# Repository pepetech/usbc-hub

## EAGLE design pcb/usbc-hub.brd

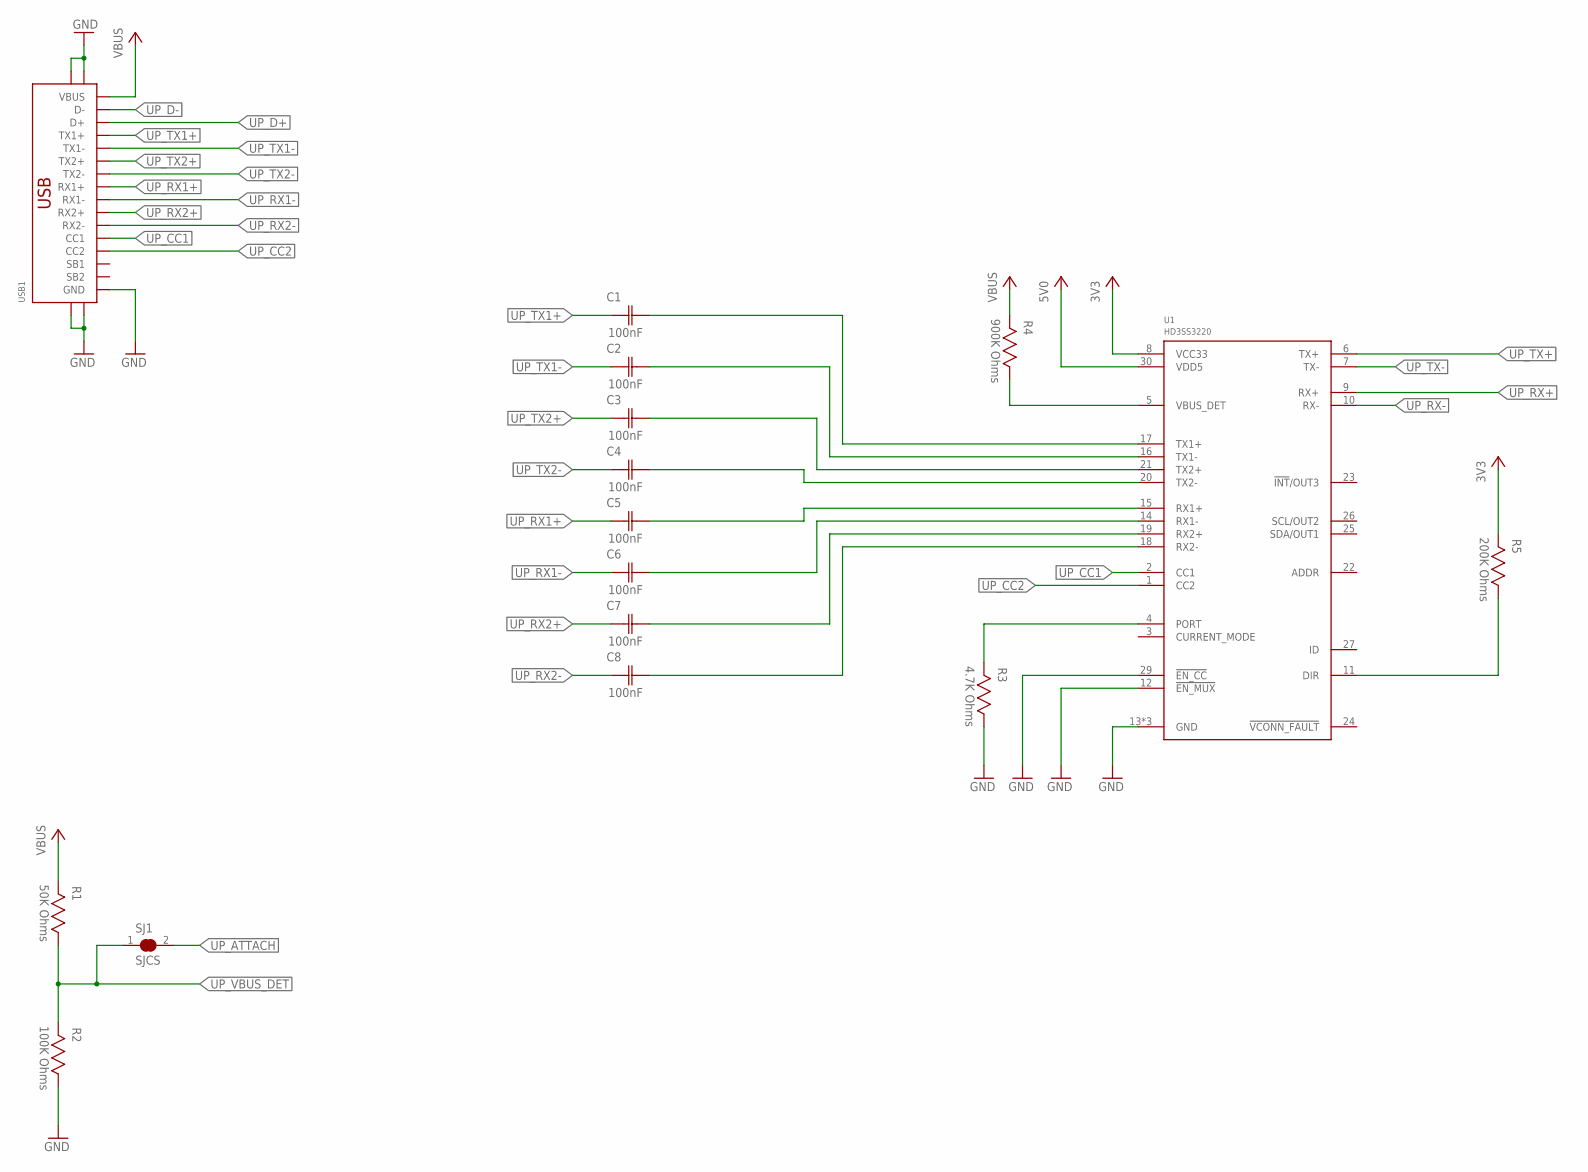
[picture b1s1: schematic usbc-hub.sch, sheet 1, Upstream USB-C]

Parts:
C1, C2, C3, C4, C5, C6, C7, C8: 100nF; CAP0603
R1: 50K Ohms; RES0603
R2: 100K Ohms; RES0603
R3: 4.7K Ohms; RES0603
R4: 900K Ohms; RES0603
R5: 200K Ohms; RES0603
SJ1: SJCS; SJC_S
U1: HD3SS3220; WQFN30
USB1: USB-C-24P-SMD-FLAT-SIDE

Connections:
3V3: R5.2, U1.8 (VCC33); also elsewhere on the board
5V0: U1.30 (VDD5); also elsewhere on the board
DN2_PWR_EN1: R1.2
GND: R2.1, R3.1, U1.12 (!EN_MUX), U1.13 (GND), U1.28 (GND), U1.29 (!EN_CC), U1.31 (GND), USB1.A1 (GND), USB1.A12 (GND), USB1.B1 (GND), USB1.B12 (GND), USB1.SHIELD@0 (SHIELD), USB1.SHIELD@1 (SHIELD), USB1.SHIELD@2 (SHIELD), USB1.SHIELD@3 (SHIELD); also elsewhere on the board
unnamed: C1.2 (C2), U1.17 (TX1+)
unnamed: C2.2 (C2), U1.16 (TX1-)
unnamed: C3.2 (C2), U1.21 (TX2+)
unnamed: C4.2 (C2), U1.20 (TX2-)
unnamed: C5.2 (C2), U1.15 (RX1+)
unnamed: C6.2 (C2), U1.14 (RX1-)
unnamed: C7.2 (C2), U1.19 (RX2+)
unnamed: C8.2 (C2), U1.18 (RX2-)
unnamed: R4.1, U1.5 (VBUS_DET)
unnamed: R3.2, U1.4 (PORT)
unnamed: R5.1, U1.11 (DIR)
UP_ATTACH: SJ1.2; also elsewhere on the board
UP_CC1: U1.2 (CC1), USB1.A5 (CC1)
UP_CC2: U1.1 (CC2), USB1.B5 (CC2)
UP_D+: USB1.A6 (D+), USB1.B6 (D+); also elsewhere on the board
UP_D-: USB1.A7 (D-), USB1.B7 (D-); also elsewhere on the board
UP_RX1+: C5.1 (C1), USB1.B11 (RX1+)
UP_RX1-: C6.1 (C1), USB1.B10 (RX1-)
UP_RX2+: C7.1 (C1), USB1.A11 (RX2+)
UP_RX2-: C8.1 (C1), USB1.A10 (RX2-)
UP_RX+: U1.9 (RX+); also elsewhere on the board
UP_RX-: U1.10 (RX-); also elsewhere on the board
UP_TX1+: C1.1 (C1), USB1.A2 (TX1+)
UP_TX1-: C2.1 (C1), USB1.A3 (TX1-)
UP_TX2+: C3.1 (C1), USB1.B2 (TX2+)
UP_TX2-: C4.1 (C1), USB1.B3 (TX2-)
UP_TX+: U1.6 (TX+); also elsewhere on the board
UP_TX-: U1.7 (TX-); also elsewhere on the board
UP_VBUS_DET: R1.1, R2.2, SJ1.1; also elsewhere on the board
VBUS: R4.2, USB1.A4 (VBUS), USB1.A9 (VBUS), USB1.B4 (VBUS), USB1.B9 (VBUS); also elsewhere on the board

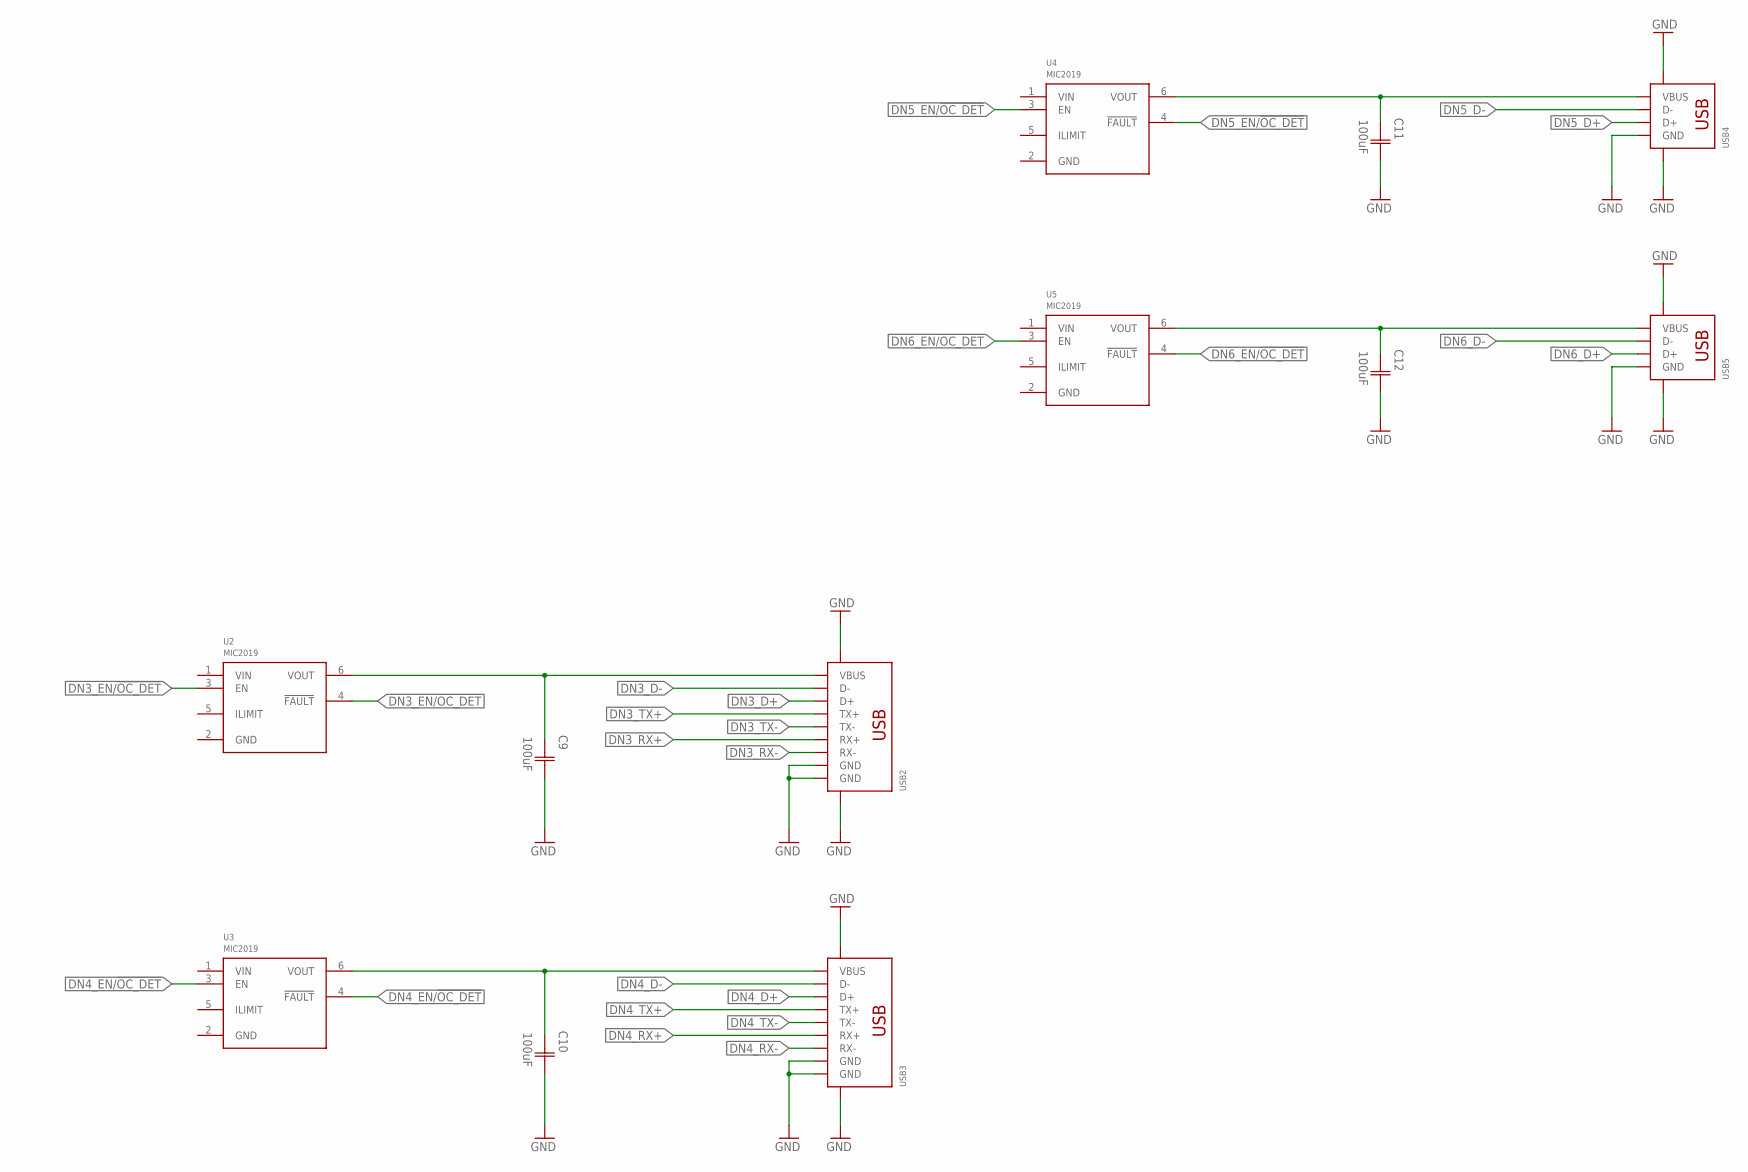
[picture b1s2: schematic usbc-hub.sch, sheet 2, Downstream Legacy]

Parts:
C9, C10, C11, C12: 100uF; CAP1206
U2, U3, U4, U5: MIC2019; SOT23-6
USB2, USB3: USB3-A-TH-FLAT-SIDE
USB4, USB5: USB-A-TH-FLAT-SIDE

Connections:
DN3_D+: USB2.D+; also elsewhere on the board
DN3_D-: USB2.D-; also elsewhere on the board
DN3_EN/!OC_DET: U2.3 (EN), U2.4 (!FAULT); also elsewhere on the board
DN3_RX+: USB2.RX+; also elsewhere on the board
DN3_RX-: USB2.RX-; also elsewhere on the board
DN3_TX+: USB2.TX+; also elsewhere on the board
DN3_TX-: USB2.TX-; also elsewhere on the board
DN4_D+: USB3.D+; also elsewhere on the board
DN4_D-: USB3.D-; also elsewhere on the board
DN4_EN/!OC_DET: U3.3 (EN), U3.4 (!FAULT); also elsewhere on the board
DN4_RX+: USB3.RX+; also elsewhere on the board
DN4_RX-: USB3.RX-; also elsewhere on the board
DN4_TX+: USB3.TX+; also elsewhere on the board
DN4_TX-: USB3.TX-; also elsewhere on the board
DN5_D+: USB4.D+; also elsewhere on the board
DN5_D-: USB4.D-; also elsewhere on the board
DN5_EN/!OC_DET: U4.3 (EN), U4.4 (!FAULT); also elsewhere on the board
DN6_D+: USB5.D+; also elsewhere on the board
DN6_D-: USB5.D-; also elsewhere on the board
DN6_EN/!OC_DET: U5.3 (EN), U5.4 (!FAULT); also elsewhere on the board
GND: C9.2 (C2), C10.2 (C2), C11.2 (C2), C12.2 (C2), USB2.GND, USB2.P$10 (SHIELD), USB2.P$11 (SHIELD), USB2.SS_GND (GND), USB3.GND, USB3.P$10 (SHIELD), USB3.P$11 (SHIELD), USB3.SS_GND (GND), USB4.GND, USB4.P$5 (SHIELD), USB4.P$6 (SHIELD), USB5.GND, USB5.P$5 (SHIELD), USB5.P$6 (SHIELD); also elsewhere on the board
unnamed: C9.1 (C1), U2.6 (VOUT), USB2.VBUS
unnamed: C12.1 (C1), U5.6 (VOUT), USB5.VBUS
unnamed: C11.1 (C1), U4.6 (VOUT), USB4.VBUS
unnamed: C10.1 (C1), U3.6 (VOUT), USB3.VBUS

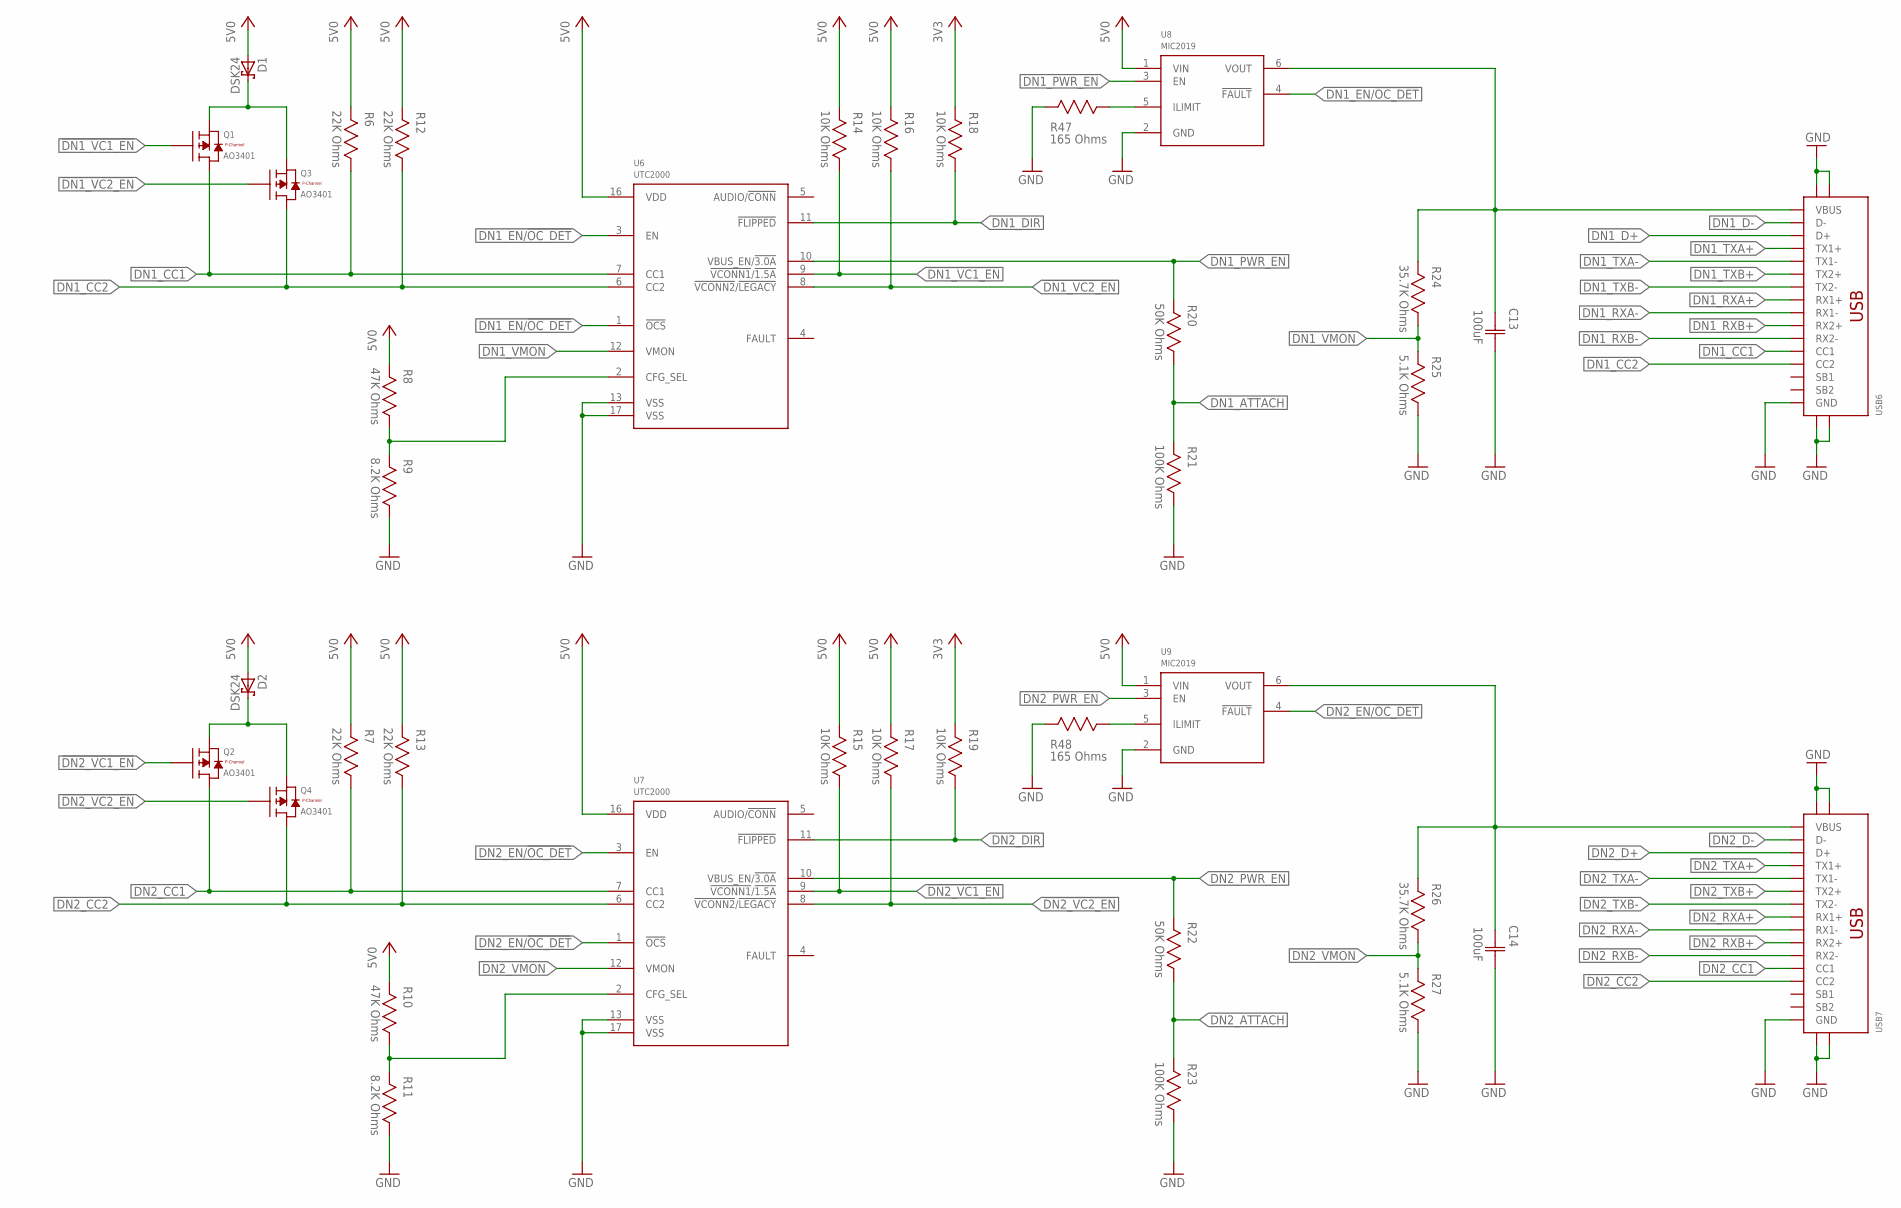
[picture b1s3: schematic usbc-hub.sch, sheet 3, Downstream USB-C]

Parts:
C13, C14: 100uF; CAP1206
D1, D2: DSK24; SOD-123F
Q1, Q2, Q3, Q4: AO3401; SOT23
R6, R7, R12, R13: 22K Ohms; RES0603
R8, R10: 47K Ohms; RES0603
R9, R11: 8.2K Ohms; RES0603
R14, R15, R16, R17, R18, R19: 10K Ohms; RES0603
R20, R22: 50K Ohms; RES0603
R21, R23: 100K Ohms; RES0603
R24, R26: 35.7K Ohms; RES0603
R25, R27: 5.1K Ohms; RES0603
R47, R48: 165 Ohms; RES0603
U6, U7: UTC2000; QFN16
U8, U9: MIC2019; SOT23-6
USB6, USB7: USB-C-24P-SMD-FLAT-SIDE

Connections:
3V3: R18.2, R19.2; also elsewhere on the board
5V0: D1.A, D2.A, R6.2, R7.2, R8.2, R10.2, R12.2, R13.2, R14.2, R15.2, R16.2, R17.2, U6.16 (VDD), U7.16 (VDD), U8.1 (VIN), U9.1 (VIN); also elsewhere on the board
!DN1_VC1_EN: Q1.1 (G), R14.1, U6.9 (!VCONN1!/!1.5A)
!DN1_VC2_EN: Q3.1 (G), R16.1, U6.8 (!VCONN2!/!LEGACY)
!DN2_VC1_EN: Q2.1 (G), R15.1, U7.9 (!VCONN1!/!1.5A)
!DN2_VC2_EN: Q4.1 (G), R17.1, U7.8 (!VCONN2!/!LEGACY)
DN1_ATTACH: R20.1, R21.2; also elsewhere on the board
DN1_CC1: Q1.3 (D), R6.1, U6.7 (CC1), USB6.A5 (CC1)
DN1_CC2: Q3.3 (D), R12.1, U6.6 (CC2), USB6.B5 (CC2)
DN1_D+: USB6.A6 (D+), USB6.B6 (D+); also elsewhere on the board
DN1_D-: USB6.A7 (D-), USB6.B7 (D-); also elsewhere on the board
DN1_DIR: R18.1, U6.11 (!FLIPPED); also elsewhere on the board
DN1_EN/!OC_DET: U6.1 (!OCS), U6.3 (EN), U8.4 (!FAULT); also elsewhere on the board
DN1_PWR_EN: R20.2, U6.10 (VBUS_EN/!3.0A), U8.3 (EN)
DN1_RXA+: USB6.B11 (RX1+); also elsewhere on the board
DN1_RXA-: USB6.B10 (RX1-); also elsewhere on the board
DN1_RXB+: USB6.A11 (RX2+); also elsewhere on the board
DN1_RXB-: USB6.A10 (RX2-); also elsewhere on the board
DN1_TXA+: USB6.A2 (TX1+); also elsewhere on the board
DN1_TXA-: USB6.A3 (TX1-); also elsewhere on the board
DN1_TXB+: USB6.B2 (TX2+); also elsewhere on the board
DN1_TXB-: USB6.B3 (TX2-); also elsewhere on the board
DN1_VMON: R24.1, R25.2, U6.12 (VMON)
DN2_ATTACH: R22.1, R23.2; also elsewhere on the board
DN2_CC1: Q2.3 (D), R7.1, U7.7 (CC1), USB7.A5 (CC1)
DN2_CC2: Q4.3 (D), R13.1, U7.6 (CC2), USB7.B5 (CC2)
DN2_D+: USB7.A6 (D+), USB7.B6 (D+); also elsewhere on the board
DN2_D-: USB7.A7 (D-), USB7.B7 (D-); also elsewhere on the board
DN2_DIR: R19.1, U7.11 (!FLIPPED); also elsewhere on the board
DN2_EN/!OC_DET: U7.1 (!OCS), U7.3 (EN), U9.4 (!FAULT); also elsewhere on the board
DN2_PWR_EN: R22.2, U7.10 (VBUS_EN/!3.0A), U9.3 (EN)
DN2_RXA+: USB7.B11 (RX1+); also elsewhere on the board
DN2_RXA-: USB7.B10 (RX1-); also elsewhere on the board
DN2_RXB+: USB7.A11 (RX2+); also elsewhere on the board
DN2_RXB-: USB7.A10 (RX2-); also elsewhere on the board
DN2_TXA+: USB7.A2 (TX1+); also elsewhere on the board
DN2_TXA-: USB7.A3 (TX1-); also elsewhere on the board
DN2_TXB+: USB7.B2 (TX2+); also elsewhere on the board
DN2_TXB-: USB7.B3 (TX2-); also elsewhere on the board
DN2_VMON: R26.1, R27.2, U7.12 (VMON)
GND: C13.2 (C2), C14.2 (C2), R9.1, R11.1, R21.1, R23.1, R25.1, R27.1, R47.2, R48.2, U6.13 (VSS), U6.17 (VSS), U7.13 (VSS), U7.17 (VSS), U8.2 (GND), U9.2 (GND), USB6.A1 (GND), USB6.A12 (GND), USB6.B1 (GND), USB6.B12 (GND), USB6.SHIELD@0 (SHIELD), USB6.SHIELD@1 (SHIELD), USB6.SHIELD@2 (SHIELD), USB6.SHIELD@3 (SHIELD), USB7.A1 (GND), USB7.A12 (GND), USB7.B1 (GND), USB7.B12 (GND), USB7.SHIELD@0 (SHIELD), USB7.SHIELD@1 (SHIELD), USB7.SHIELD@2 (SHIELD), USB7.SHIELD@3 (SHIELD); also elsewhere on the board
unnamed: C14.1 (C1), U9.6 (VOUT), USB7.A4 (VBUS), USB7.A9 (VBUS), USB7.B4 (VBUS), USB7.B9 (VBUS)
unnamed: C13.1 (C1), R24.2, U8.6 (VOUT), USB6.A4 (VBUS), USB6.A9 (VBUS), USB6.B4 (VBUS), USB6.B9 (VBUS)
unnamed: D2.C, Q2.2 (S), Q4.2 (S)
unnamed: D1.C, Q1.2 (S), Q3.2 (S)
unnamed: R10.1, R11.2, U7.2 (CFG_SEL)
unnamed: R8.1, R9.2, U6.2 (CFG_SEL)
unnamed: R47.1, U8.5 (ILIMIT)
unnamed: R48.1, U9.5 (ILIMIT)

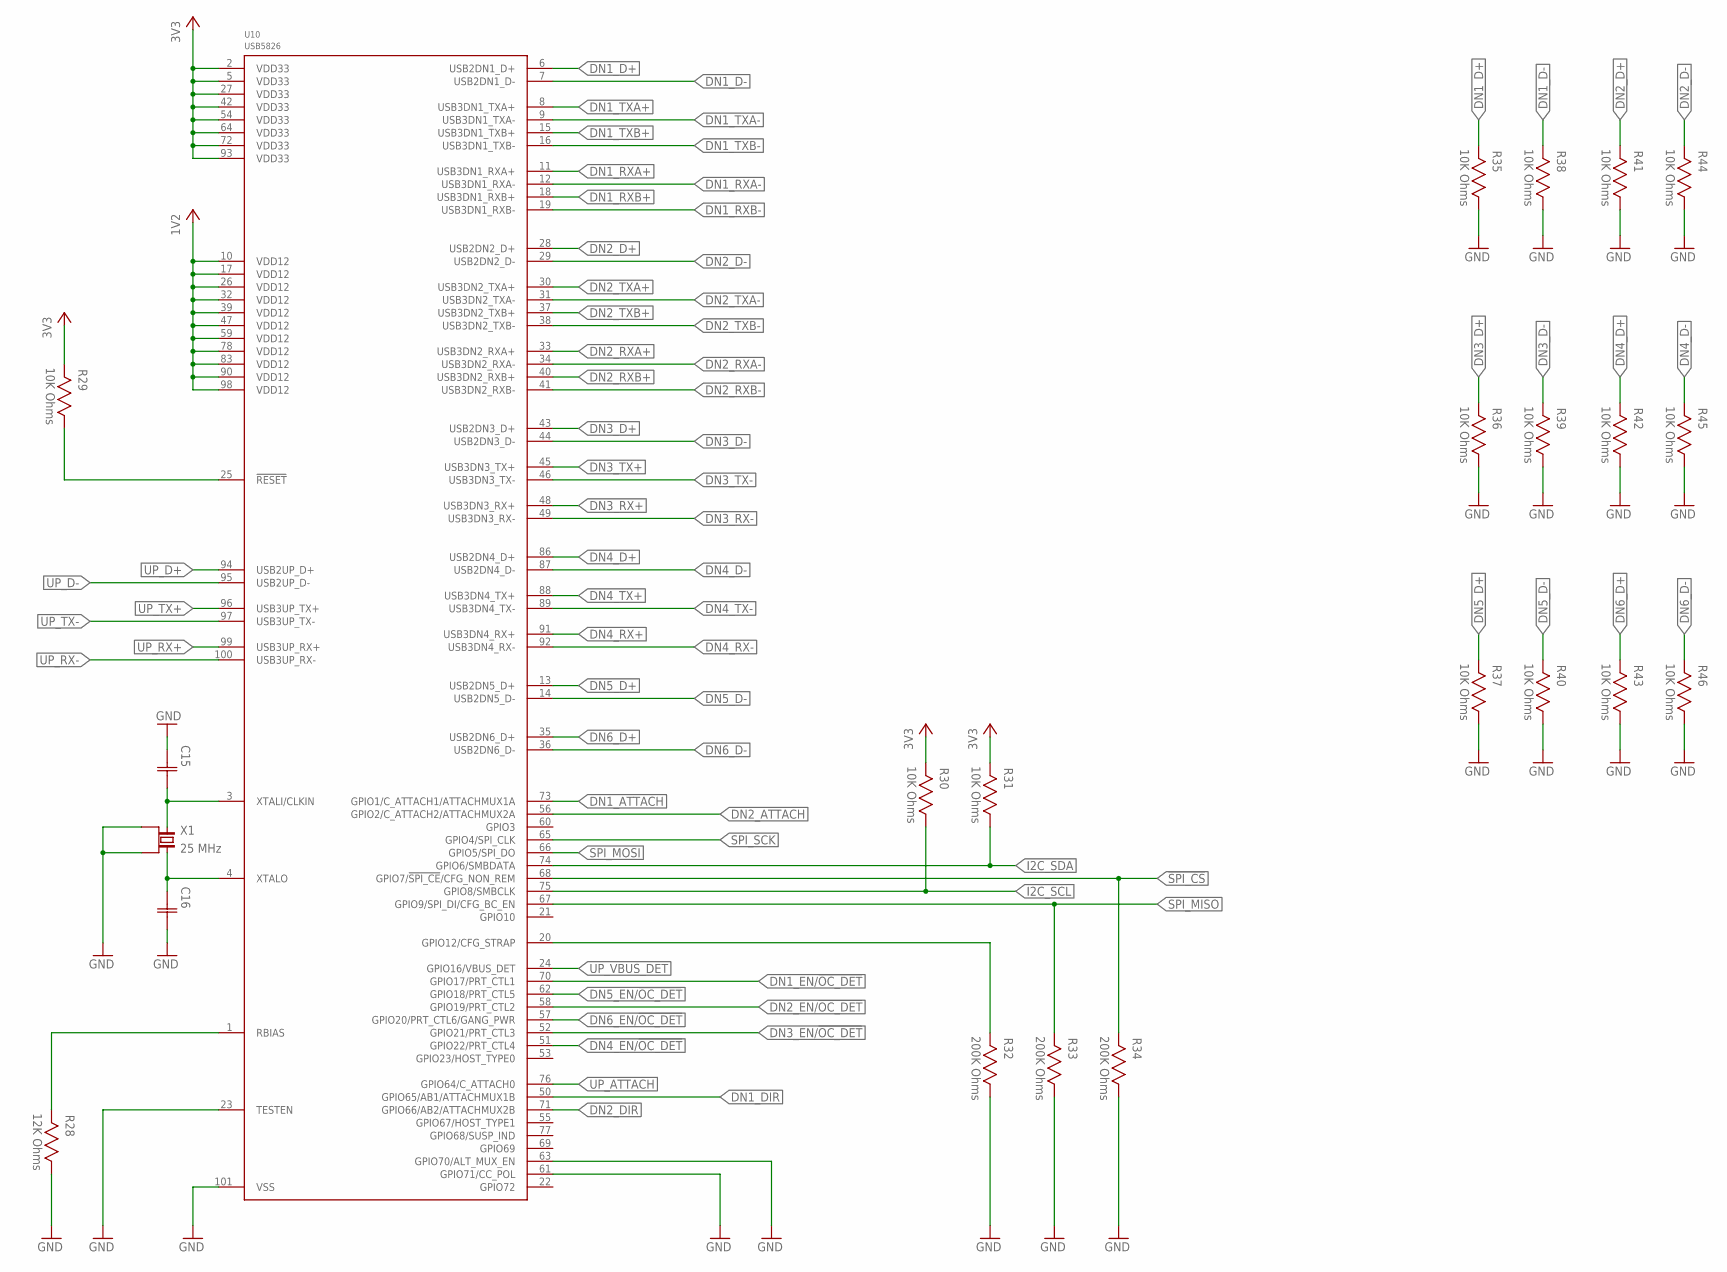
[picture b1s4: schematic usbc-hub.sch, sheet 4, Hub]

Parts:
C15, C16: CAPACITOR-0603; CAP0603
R28: 12K Ohms; RES0603
R29, R30, R31, R35, R36, R37, R38, R39, R40, R41, R42, R43, R44, R45, R46: 10K Ohms; RES0603
R32, R33, R34: 200K Ohms; RES0603
U10: USB5826; VQFN100
X1: 25 MHz; 4-SMD-3225

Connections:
1V2: U10.10 (VDD12), U10.17 (VDD12), U10.26 (VDD12), U10.32 (VDD12), U10.39 (VDD12), U10.47 (VDD12), U10.59 (VDD12), U10.78 (VDD12), U10.83 (VDD12), U10.90 (VDD12), U10.98 (VDD12)
3V3: R29.2, R30.2, R31.2, U10.2 (VDD33), U10.5 (VDD33), U10.27 (VDD33), U10.42 (VDD33), U10.54 (VDD33), U10.64 (VDD33), U10.72 (VDD33), U10.93 (VDD33); also elsewhere on the board
!SPI_CS: R34.2, U10.68 (GPIO7/!SPI_CE!/CFG_NON_REM)
DN1_ATTACH: U10.73 (GPIO1/C_ATTACH1/ATTACHMUX1A); also elsewhere on the board
DN1_D+: R35.2, U10.6 (USB2DN1_D+); also elsewhere on the board
DN1_D-: R38.2, U10.7 (USB2DN1_D-); also elsewhere on the board
DN1_DIR: U10.50 (GPIO65/AB1/ATTACHMUX1B); also elsewhere on the board
DN1_EN/!OC_DET: U10.70 (GPIO17/PRT_CTL1); also elsewhere on the board
DN1_RXA+: U10.11 (USB3DN1_RXA+); also elsewhere on the board
DN1_RXA-: U10.12 (USB3DN1_RXA-); also elsewhere on the board
DN1_RXB+: U10.18 (USB3DN1_RXB+); also elsewhere on the board
DN1_RXB-: U10.19 (USB3DN1_RXB-); also elsewhere on the board
DN1_TXA+: U10.8 (USB3DN1_TXA+); also elsewhere on the board
DN1_TXA-: U10.9 (USB3DN1_TXA-); also elsewhere on the board
DN1_TXB+: U10.15 (USB3DN1_TXB+); also elsewhere on the board
DN1_TXB-: U10.16 (USB3DN1_TXB-); also elsewhere on the board
DN2_ATTACH: U10.56 (GPIO2/C_ATTACH2/ATTACHMUX2A); also elsewhere on the board
DN2_D+: R41.2, U10.28 (USB2DN2_D+); also elsewhere on the board
DN2_D-: R44.2, U10.29 (USB2DN2_D-); also elsewhere on the board
DN2_DIR: U10.71 (GPIO66/AB2/ATTACHMUX2B); also elsewhere on the board
DN2_EN/!OC_DET: U10.58 (GPIO19/PRT_CTL2); also elsewhere on the board
DN2_RXA+: U10.33 (USB3DN2_RXA+); also elsewhere on the board
DN2_RXA-: U10.34 (USB3DN2_RXA-); also elsewhere on the board
DN2_RXB+: U10.40 (USB3DN2_RXB+); also elsewhere on the board
DN2_RXB-: U10.41 (USB3DN2_RXB-); also elsewhere on the board
DN2_TXA+: U10.30 (USB3DN2_TXA+); also elsewhere on the board
DN2_TXA-: U10.31 (USB3DN2_TXA-); also elsewhere on the board
DN2_TXB+: U10.37 (USB3DN2_TXB+); also elsewhere on the board
DN2_TXB-: U10.38 (USB3DN2_TXB-); also elsewhere on the board
DN3_D+: R36.2, U10.43 (USB2DN3_D+); also elsewhere on the board
DN3_D-: R39.2, U10.44 (USB2DN3_D-); also elsewhere on the board
DN3_EN/!OC_DET: U10.52 (GPIO21/PRT_CTL3); also elsewhere on the board
DN3_RX+: U10.48 (USB3DN3_RX+); also elsewhere on the board
DN3_RX-: U10.49 (USB3DN3_RX-); also elsewhere on the board
DN3_TX+: U10.45 (USB3DN3_TX+); also elsewhere on the board
DN3_TX-: U10.46 (USB3DN3_TX-); also elsewhere on the board
DN4_D+: R42.2, U10.86 (USB2DN4_D+); also elsewhere on the board
DN4_D-: R45.2, U10.87 (USB2DN4_D-); also elsewhere on the board
DN4_EN/!OC_DET: U10.51 (GPIO22/PRT_CTL4); also elsewhere on the board
DN4_RX+: U10.91 (USB3DN4_RX+); also elsewhere on the board
DN4_RX-: U10.92 (USB3DN4_RX-); also elsewhere on the board
DN4_TX+: U10.88 (USB3DN4_TX+); also elsewhere on the board
DN4_TX-: U10.89 (USB3DN4_TX-); also elsewhere on the board
DN5_D+: R37.2, U10.13 (USB2DN5_D+); also elsewhere on the board
DN5_D-: R40.2, U10.14 (USB2DN5_D-); also elsewhere on the board
DN5_EN/!OC_DET: U10.62 (GPIO18/PRT_CTL5); also elsewhere on the board
DN6_D+: R43.2, U10.35 (USB2DN6_D+); also elsewhere on the board
DN6_D-: R46.2, U10.36 (USB2DN6_D-); also elsewhere on the board
DN6_EN/!OC_DET: U10.57 (GPIO20/PRT_CTL6/GANG_PWR); also elsewhere on the board
GND: C15.1 (C1), C16.2 (C2), R28.1, R32.1, R33.1, R34.1, R35.1, R36.1, R37.1, R38.1, R39.1, R40.1, R41.1, R42.1, R43.1, R44.1, R45.1, R46.1, U10.23 (TESTEN), U10.61 (GPIO71/CC_POL), U10.63 (GPIO70/ALT_MUX_EN), U10.101 (VSS), X1.2 (GND), X1.4 (GND); also elsewhere on the board
I2C_SCL: R30.1, U10.75 (GPIO8/SMBCLK)
I2C_SDA: R31.1, U10.74 (GPIO6/SMBDATA)
unnamed: C16.1 (C1), U10.4 (XTALO), X1.3 (2)
unnamed: C15.2 (C2), U10.3 (XTALI/CLKIN), X1.1
unnamed: R32.2, U10.20 (GPIO12/CFG_STRAP)
unnamed: R29.1, U10.25 (!RESET)
unnamed: R28.2, U10.1 (RBIAS)
SPI_MISO: R33.2, U10.67 (GPIO9/SPI_DI/CFG_BC_EN)
SPI_MOSI: U10.66 (GPIO5/SPI_DO)
SPI_SCK: U10.65 (GPIO4/SPI_CLK)
UP_ATTACH: U10.76 (GPIO64/C_ATTACH0); also elsewhere on the board
UP_D+: U10.94 (USB2UP_D+); also elsewhere on the board
UP_D-: U10.95 (USB2UP_D-); also elsewhere on the board
UP_RX+: U10.99 (USB3UP_RX+); also elsewhere on the board
UP_RX-: U10.100 (USB3UP_RX-); also elsewhere on the board
UP_TX+: U10.96 (USB3UP_TX+); also elsewhere on the board
UP_TX-: U10.97 (USB3UP_TX-); also elsewhere on the board
UP_VBUS_DET: U10.24 (GPIO16/VBUS_DET); also elsewhere on the board

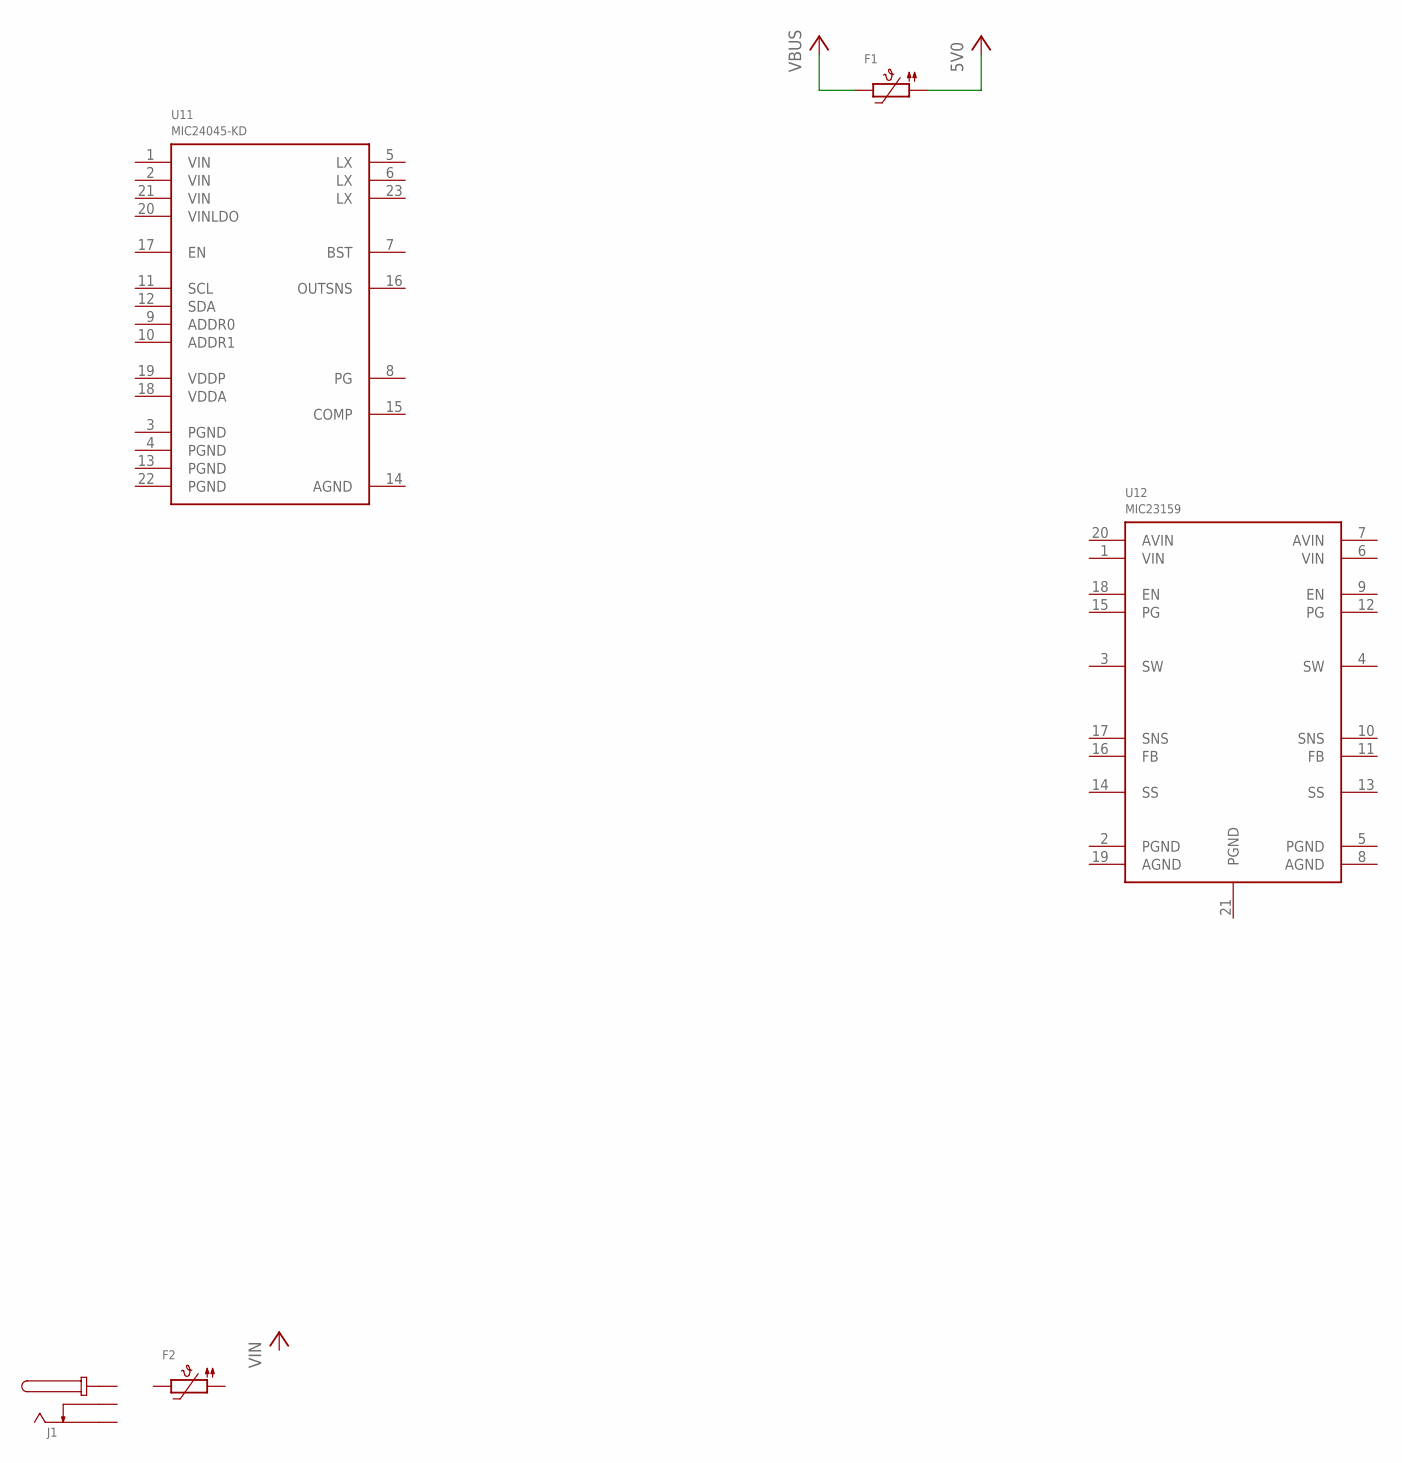
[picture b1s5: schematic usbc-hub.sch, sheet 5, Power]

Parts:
F1, F2: PTC1812; 1812
J1: DCJACK; DC-050
U11: MIC24045-KD; FQFN20
U12: MIC23159; VQFN20

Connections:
5V0: F1.1; also elsewhere on the board
VBUS: F1.2; also elsewhere on the board

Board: 2 copper layers, 94 parts (0 on the bottom side), 113 nets, no tracks yet.

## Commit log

2019-06-15 Schematic almost complete
2019-06-15 Work on power
